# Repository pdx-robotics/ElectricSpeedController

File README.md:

# ElectricSpeedController
repo to store the blueprints, schematic, code, etc. relating to the development of an ESC

Here are some good guides on how to use Eagle Cad  
https://learn.sparkfun.com/tutorials/how-to-install-and-setup-eagle  
https://learn.sparkfun.com/tutorials/using-eagle-schematic  
https://learn.sparkfun.com/tutorials/using-eagle-board-layout  
https://learn.sparkfun.com/tutorials/designing-pcbs-advanced-smd  
https://learn.sparkfun.com/tutorials/designing-pcbs-smd-footprints  
https://learn.sparkfun.com/tutorials/making-custom-footprints-in-eagle  
https://learn.sparkfun.com/tutorials/importing-custom-images-into-eagle

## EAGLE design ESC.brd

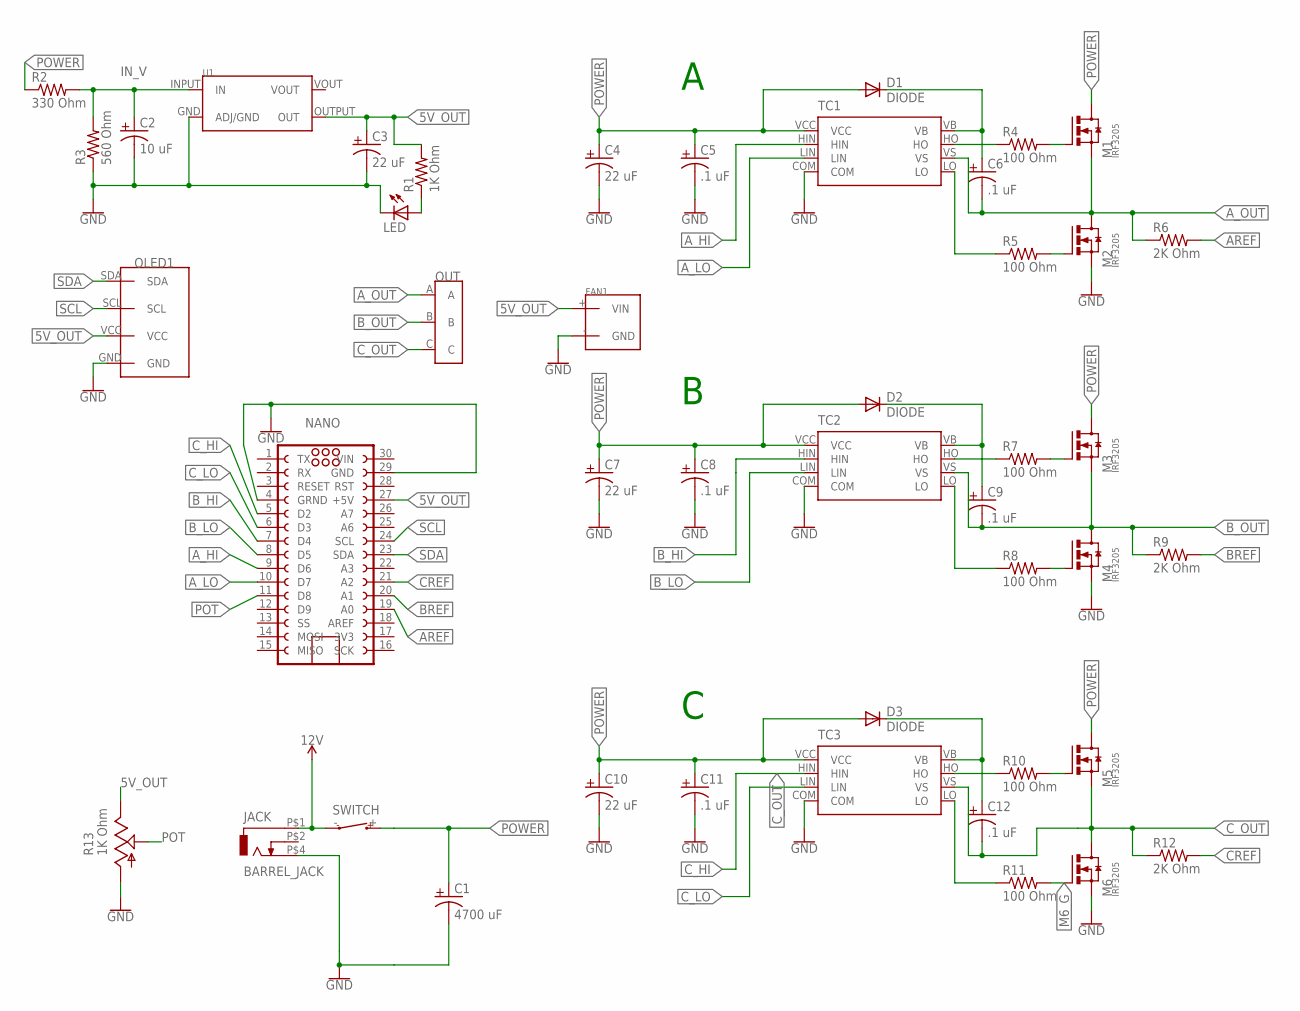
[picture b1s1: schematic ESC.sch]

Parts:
C1: 4700 uF; CAP_LARGE
C2: 10 uF; 0805
C3, C4, C7, C10: 22 uF; 0805
C5, C6, C8, C9, C11, C12: .1 uF; 0805
D1, D2, D3: DIODE
FAN1: 2P_POWER
JACK: BARREL_JACK
LED: LED; LED_PADS
M1, M2, M3, M4, M5, M6: IRF3205
NANO: ARDUINO_NANO_CONNECTOR; ARDUINO_NANO_HEADER
OLED1: I2C_OLED_4PIN_HEADER; OLED_CONNECTION
OUT: TERMINAL3; 3PIN_TERMINAL
R1: 1K Ohm; 0805
R2: 330 Ohm; RESISTOR
R3: 560 Ohm; RESISTOR
R4, R5, R7, R8, R10, R11: 100 Ohm; 0805
R6, R9, R12: 2K Ohm; 0805
R13: 1K Ohm; POT
SWITCH: BOAT_SWITCH; 2P_POWER
TC1, TC2, TC3: TSC428CPA; PDIP-8_N
U1: AZ1117CH

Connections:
3V3: NANO.17 (3V3)
5V_OUT: C3.1 (ANODE), FAN1.+ (VIN), NANO.27 (+5V), OLED1.VCC, R1.2, R13.+, U1.OUTPUT (OUT)
12V: JACK.P$1 (1), SWITCH.-
AREF: NANO.19 (A0), R6.2
A_HI: NANO.9 (D6), TC1.HIN
A_LO: NANO.10 (D7), TC1.LIN
A_OUT: C6.2 (CATHODE), M1.SOURCE (S), M2.DRAIN (D), OUT.A, R6.1, TC1.VS
BREF: NANO.20 (A1), R9.2
B_HI: NANO.7 (D4), TC2.HIN
B_LO: NANO.8 (D5), TC2.LIN
B_OUT: C9.2 (CATHODE), M3.SOURCE (S), M4.DRAIN (D), OUT.B, R9.1, TC2.VS
CREF: NANO.21 (A2), R12.2
C_HI: NANO.5 (D2), TC3.HIN
C_LO: NANO.6 (D3), TC3.LIN
C_OUT: C12.2 (CATHODE), M5.SOURCE (S), M6.DRAIN (D), OUT.C, R12.1, TC3.VS
GND: C1.CATHODE, C2.2 (CATHODE), C3.2 (CATHODE), C4.2 (CATHODE), C5.2 (CATHODE), C7.2 (CATHODE), C8.2 (CATHODE), C10.2 (CATHODE), C11.2 (CATHODE), FAN1.- (GND), JACK.P$4 (3), LED.C, M2.SOURCE (S), M4.SOURCE (S), M6.SOURCE (S), NANO.4 (GRND), NANO.29 (GND), OLED1.GND, R3.P$1 (1), R13.-, TC1.COM, TC2.COM, TC3.COM, U1.GND (ADJ/GND)
IN_V: C2.1 (ANODE), R2.P$2 (2), R3.P$2 (2), U1.INPUT (IN)
M6_G: M6.GATE (G), R11.2
unnamed: M2.GATE (G), R5.2
unnamed: LED.A, R1.1
unnamed: R4.1, TC1.HO
unnamed: M1.GATE (G), R4.2
unnamed: R5.1, TC1.LO
unnamed: C6.1 (ANODE), D1.C, TC1.VB
unnamed: M3.GATE (G), R7.2
unnamed: M4.GATE (G), R8.2
unnamed: R7.1, TC2.HO
unnamed: R8.1, TC2.LO
unnamed: C9.1 (ANODE), D2.C, TC2.VB
unnamed: M5.GATE (G), R10.2
unnamed: R10.1, TC3.HO
unnamed: R11.1, TC3.LO
unnamed: C12.1 (ANODE), D3.C, TC3.VB
POT: NANO.11 (D8), R13.VAR
POWER: C1.ANODE, C4.1 (ANODE), C5.1 (ANODE), C7.1 (ANODE), C8.1 (ANODE), C10.1 (ANODE), C11.1 (ANODE), D1.A, D2.A, D3.A, M1.DRAIN (D), M3.DRAIN (D), M5.DRAIN (D), R2.P$1 (1), SWITCH.+, TC1.VCC, TC2.VCC, TC3.VCC
SCL: NANO.24 (SCL), OLED1.SCL
SDA: NANO.23 (SDA), OLED1.SDA

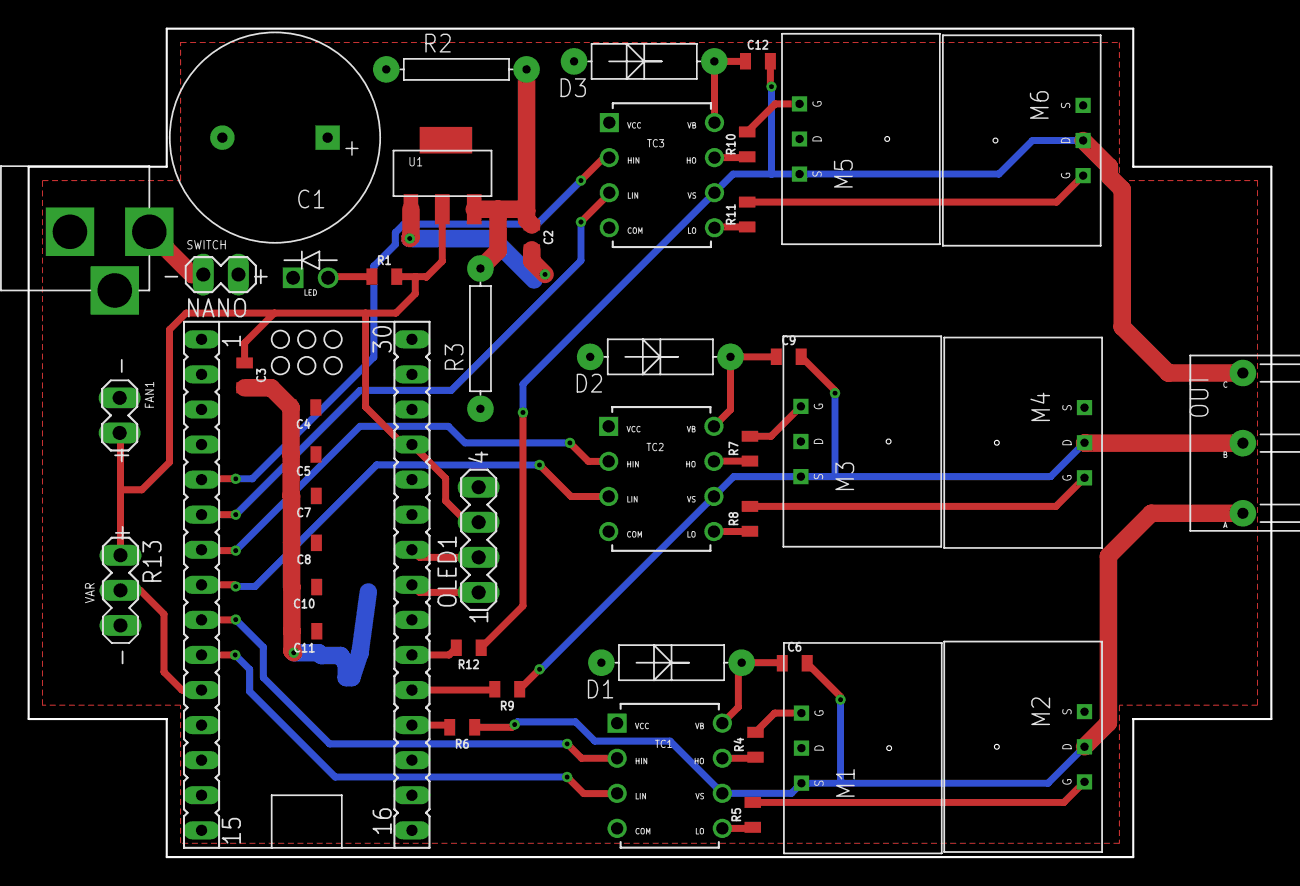
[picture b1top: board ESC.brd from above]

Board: 2 copper layers, 90.0 x 60.0 mm, 45 parts (0 on the bottom side), 36 nets.

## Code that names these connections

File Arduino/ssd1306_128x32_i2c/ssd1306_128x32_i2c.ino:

/*********************************************************************
This is an example for our Monochrome OLEDs based on SSD1306 drivers

  Pick one up today in the adafruit shop!
  ------> http://www.adafruit.com/category/63_98

This example is for a 128x32 size display using I2C to communicate
3 pins are required to interface (2 I2C and one reset)

Adafruit invests time and resources providing this open source code, 
please support Adafruit and open-source hardware by purchasing 
products from Adafruit!

Written by Limor Fried/Ladyada  for Adafruit Industries.  
BSD license, check license.txt for more information
All text above, and the splash screen must be included in any redistribution
*********************************************************************/

#include <SPI.h>
#include <Wire.h>
#include <Adafruit_GFX.h>
#include <Adafruit_SSD1306.h>

#define OLED_RESET 4
Adafruit_SSD1306 display(OLED_RESET);

#if (SSD1306_LCDHEIGHT != 32)
#error("Height incorrect, please fix Adafruit_SSD1306.h!");
#endif

int potPin = 2;    // select the input pin for the potentiometer
int val = 0;       // variable to store the value coming from the sensor

int emfA = A0;
int emfB = A1;
int emfC = A2;
int A_HI = 0;
int A_LOW = 0;
int B_HI = 0;
int B_LOW = 0;
int C_HI = 0;
int C_LOW = 0;

void setup()   {                
  Serial.begin(9600);

  // by default, we'll generate the high voltage from the 3.3v line internally! (neat!)
  display.begin(SSD1306_SWITCHCAPVCC, 0x3C);  // initialize with the I2C addr 0x3C (for the 128x32)
  // init done
  
  // Show image buffer on the display hardware.
  // Since the buffer is intialized with an Adafruit splashscreen
  // internally, this will display the splashscreen.
  display.display();
  delay(2000);

  // Clear the buffer.
  display.clearDisplay();

  // text display tests
  display.setTextSize(2);
  display.setTextColor(WHITE);  
  
  pinMode(A_HI,OUTPUT);
  pinMode(A_LOW,OUTPUT);
  pinMode(B_HI,OUTPUT);
  pinMode(B_LOW,OUTPUT);
  pinMode(C_HI,OUTPUT);
  pinMode(C_LOW,OUTPUT);
}

void loop() {
  val = analogRead(potPin);    // read the value from the potentiometer
  Delay=map(t,0,1024,1,1000); //we obtain the delay speed using the potentiometer
  //we map the values from 1 to 1000 microseaconds
  display.clearDisplay();
  display.setCursor(0,0);
  display.println(val);
  display.display();
  delay(500);
      
      
  int emA = analogRead(emfA);
  int emB = analogRead(emfB);
  int emC = analogRead(emfC);
  int sum = (emA+emB+emC)/3;  

  unsigned long currentMillis = micros();
 
  
  if(currentMillis - previousMillis >= Delay)
  {
    previousMillis += Delay;
    switch(fase)
    {
    //Phase1 C-B
      case 1:
        break;
    //Phase2 A-B
      case 2:
        break;
    //Phase3 A-C
      case 3: 
        break;   
    //Phase4 B-C
      case 4:
        break;
    //Phase5 B-A 
      case 5:
        break;
    //Phase6 C-A
      case 6:
        break;
    }
  
    if (Lastdelta < 0)
    {
      if (delta > 0)
      {
        Lastdelta=delta; //save the last delta
        fase= fase + 1;
        if (fase > 6) 
        {
          fase = 1;
        }
      }
    }//Zero cross from - to +  
    
    if (Lastdelta > 0)
    {
      if (delta < 0)
      {
        Lastdelta=delta;
        fase= fase + 1;
        if (fase > 6) 
        {
          fase = 1;
        }
      }
    }//Zero cross from + to - 
  }//Case ends
}

void PhaseCB()
{
  digitalWrite(AA1,LOW);
  digitalWrite(AA2,LOW);
  digitalWrite(BB1,LOW);
  digitalWrite(CC2,LOW);
  digitalWrite(BB2,HIGH);
  digitalWrite(CC1,HIGH);
  delta = emA-sum;
}

void PhaseCA()
{
  digitalWrite(AA1,LOW);
  digitalWrite(BB1,LOW);
  digitalWrite(BB2,LOW);
  digitalWrite(CC2,LOW);
  digitalWrite(CC1,HIGH);
  digitalWrite(AA2,HIGH);
  delta = emB-sum;
}

void PhaseBA()
{
  digitalWrite(AA1,LOW);
  digitalWrite(BB2,LOW);
  digitalWrite(CC1,LOW);
  digitalWrite(CC2,LOW);
  digitalWrite(AA2,HIGH);
  digitalWrite(BB1,HIGH);
  delta = emC-sum;
}

void PhaseBC()
{
  digitalWrite(AA1,LOW);
  digitalWrite(AA2,LOW);
  digitalWrite(BB2,LOW);
  digitalWrite(CC1,LOW);
  digitalWrite(BB1,HIGH);
  digitalWrite(CC2,HIGH);
  delta = emA-sum;
}

void AB()
{
  digitalWrite(AA2,LOW);
  digitalWrite(BB1,LOW);
  digitalWrite(CC1,LOW);
  digitalWrite(CC2,LOW);
  digitalWrite(AA1,HIGH);
  digitalWrite(BB2,HIGH);
  delta = emC-sum;
}

void PhaseAC()
{
  digitalWrite(AA2,LOW);
  digitalWrite(BB1,LOW);
  digitalWrite(BB2,LOW);
  digitalWrite(CC1,LOW);
  digitalWrite(CC2,HIGH);
  digitalWrite(AA1,HIGH);
  delta = emB-sum;
}

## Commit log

2018-08-14 REQUIRES SPARKFUN EAGLE LIBRARY FROM README TUTORIALS
2018-08-22 No longer needed
2018-08-25 reorganized file structure
2018-09-12 pre work 09112018 commit
2018-09-12 work from 09112018
2018-09-15 prepping for tinker session
2018-09-15 blank
2018-09-15 added library components
2018-09-25 lastest edits
2018-09-28 Made Evil Clone
2018-09-28 Killed evil clone, consolidated caps, fixed IRF3205
2018-09-28 Fixed resistor spacing
2018-10-02 daily updates 10022018
2018-10-04 daily changes for 10042018
2018-10-05 daily updates 10052018
2018-10-05 added pic
2018-10-06 late changes 10052018
2018-10-08 added a picture?
2018-10-09 added arduino code
2018-10-26 added datasheet
2019-04-23 finalized schematic
2019-04-27 parts library and updated schematic
2019-05-01 Board Layout v1 final

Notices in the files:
parts and their libraries:
SparkFun-PowerSymbols: Licensing: Creative Commons ShareAlike 4.0 International - https://creativecommons.org/licenses/by-sa/4.0
